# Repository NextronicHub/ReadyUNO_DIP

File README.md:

# ReadyUNO_DIP
## Description
READY-UNO is the best board to start your personal electronics projects, it is built upon the famous ARDUINO UNO, so it shares its simplicity and its flexibility. It contains also a BreadBoard with different interfaces of communication (SPI, UART, I2C and Serial communication) for easy development.
The READY-UNO can be programmed over a Serial Communication, using the ARDUINO IDE.
The READY-UNO can be powered through the barrel jack. The on-board power regulator can handle anything from 7 to 15VDC.
## Features
•	ATmega328 microcontroller with Optiboot (UNO) Bootloader                                                                         
•	Input voltage : 7 to 15V                                                                                                         
•	0-5V outputs                                                                                                                     
•	14 Digital I/O Pins (6 PWM outputs)                                                                                              
•	6 Analog Inputs                                                                                                                  
•	ISP Header                                                                                                                       
•	32k Flash Memory                                                                                                                 
•	16MHz Clock Speed                                                                                                                
•	All SMD Construction                                                                                                             
•	R3 Shield Compatible                                                                                                             
•	BreadBoard.                                                                                                                      
•	Red PCB.                                                                                                                         
•	I2C, UART and SPI.                                                                                                               
## Repository Contents

/Hardware - Design files (.brd, .sch)  
/Documentation - datasheet and examples

## Product Versions

ReadyUNO-DIP-V1 first release

## License Information

The hardware is released under [Creative Commons ShareAlike 4.0 International](https://creativecommons.org/licenses/by-sa/4.0/).

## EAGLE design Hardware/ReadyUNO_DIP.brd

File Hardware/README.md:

# Nextronic ReadyUNO DIP Design Files
The .sch and .brd files are Eagle CAD schematic and PCB design files from Nextronic. Eagle PCB Design | Schematic Editor, Layout Editor & Autorouter can be found at http://www.autodesk.com/products/eagle.

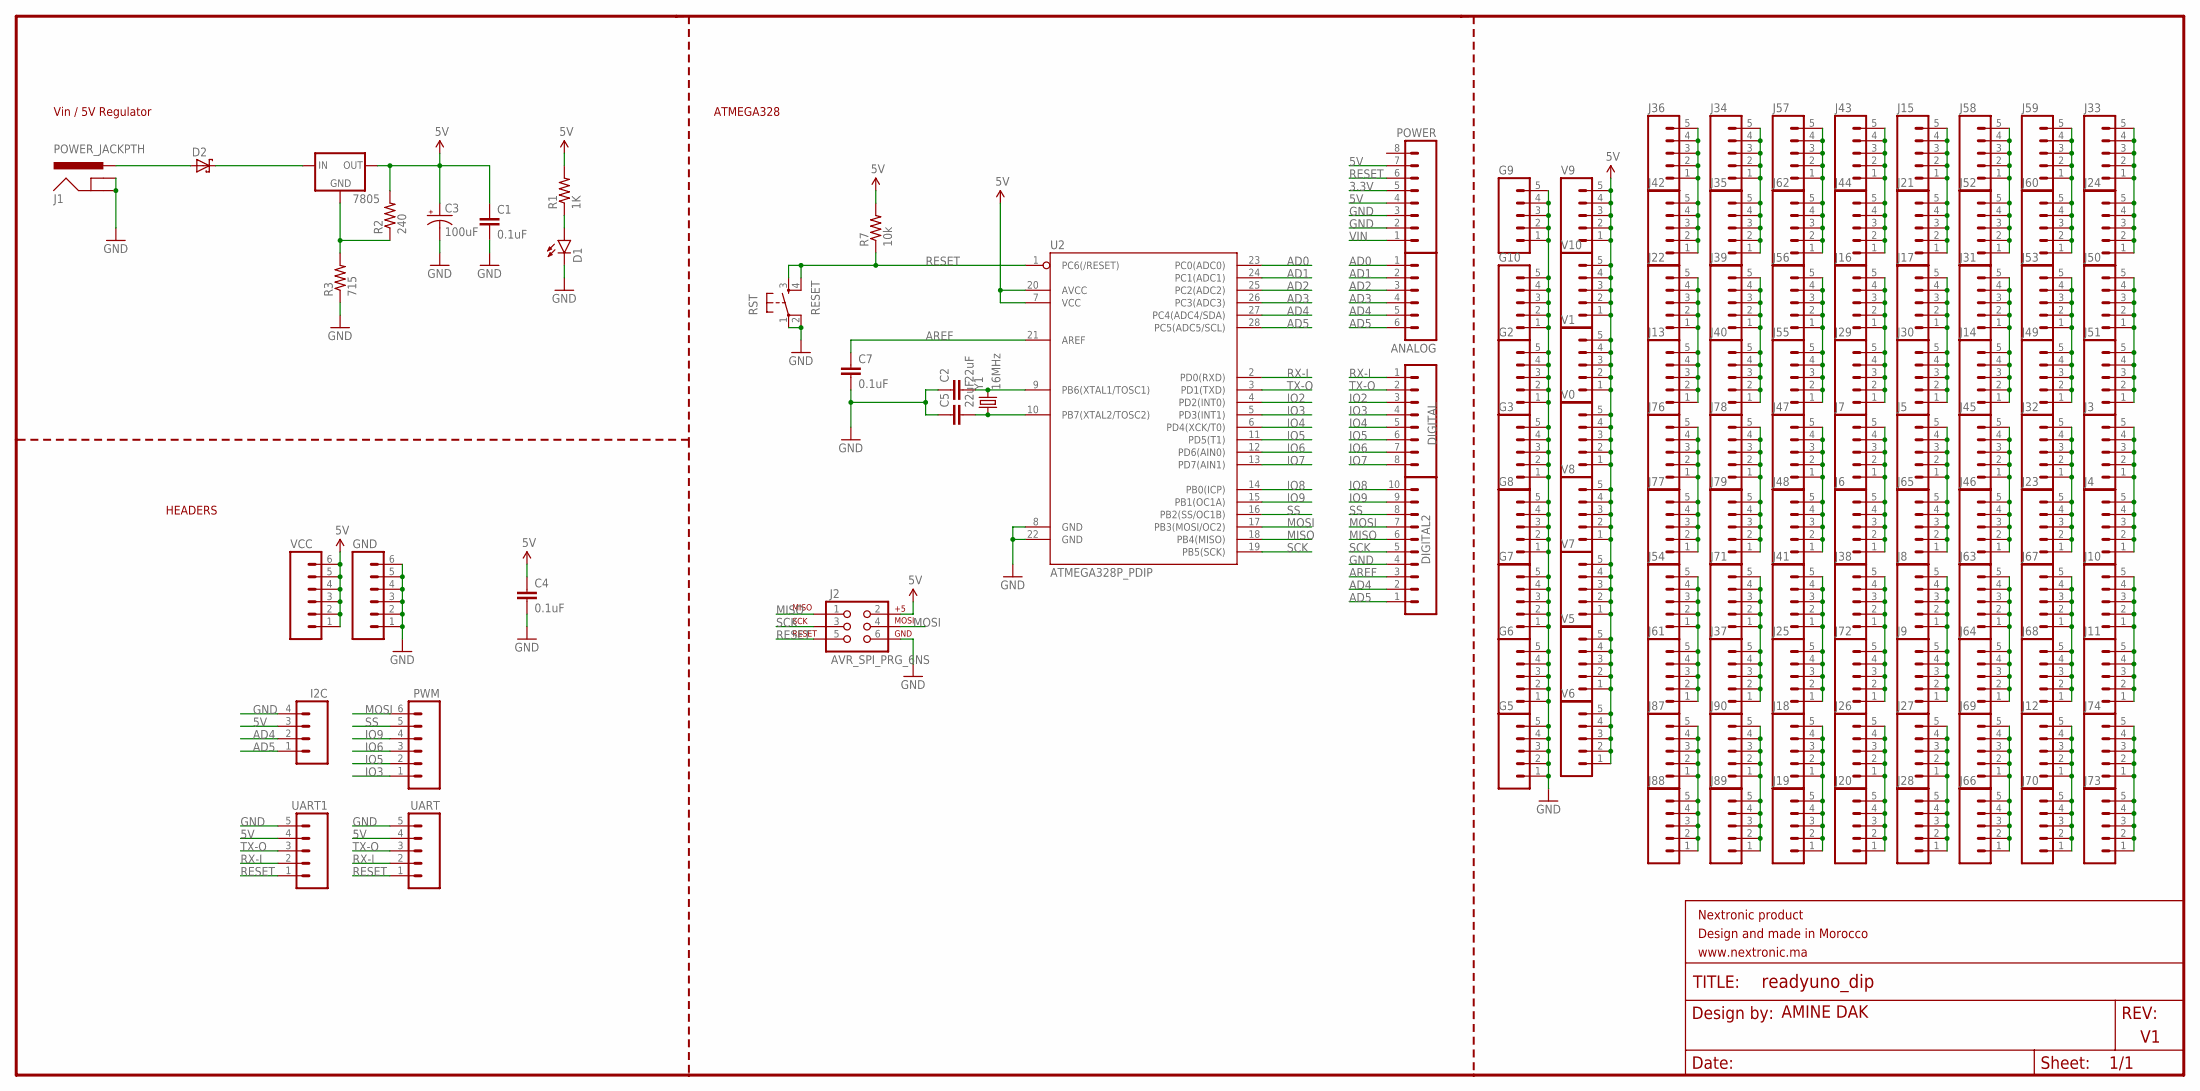
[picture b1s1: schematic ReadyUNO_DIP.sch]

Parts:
7805: V_REG_78XX-TO-220; TO-220-ALT
ANALOG: M06SILK_FEMALE_PTH; 1X06
C1, C4, C7: 0.1uF; CAP-PTH-SMALLEZ; MPN MCRR25104X7RK0050
C2, C5: 22uF; CAP-PTH-SMALLEZ; MPN MCGPR100V226M8X11
C3: 100uF; CPOL-RADIAL-100UF-25V; MPN MCGPR25V107M6.3X11
D1: LED-3MM-NO_SILK; LED3MM-NS
D2: SCHOTTKY-DIODEDO35-7; DIODE_DO35-7
DIGITAL: M08SILK_FEMALE_PTH; 1X08
DIGITAL2: M10SILK_FEMALE_PTH; 1X10
FRAME1: FRAME-LETTER; CREATIVE_COMMONS
G2, G3, G5, G6, G7, G8, G9, G10: M05PTH; 1X05
GND: M06SILK_FEMALE_PTH; 1X06
I2C: M04PTH; 1X04
J1: POWER_JACKPTH; POWER_JACK_PTH
J2: AVR_SPI_PRG_6NS; 2X3-NS
J3, J4, J5, J6, J7, J8, J9, J10, J11, J12, J13, J14, J15, J16, J17, J18, J19, J20, J21, J22, J23, J24, J25, J26, J27, J28, J29, J30, J31, J32, J33, J34, J35, J36, J37, J38, J39, J40, J41, J42, J43, J44, J45, J46, J47, J48, J49, J50, J51, J52, J53, J54, J55, J56, J57, J58, J59, J60, J61, J62, J63, J64, J65, J66, J67, J68, J69, J70, J71, J72, J73, J74, J76, J77, J78, J79, J87, J88, J89, J90: M05PTH; 1X05
POWER: M08SILK_FEMALE_PTH; 1X08
PWM: M06SILK_FEMALE_PTH; 1X06
R1: 1K; AXIAL-0.3; MPN MCRE000037
R2: 240; AXIAL-0.3; MPN MFR4-240RFI
R3: 715; AXIAL-0.3; MPN YR1B715RCC
R7: 10k; AXIAL-0.3
RST: RESET; TACTILE-PTH
U2: ATMEGA328P_PDIP; DIL28-3; MPN ATMEGA328-PU
UART, UART1: M05PTH; 1X05
V0, V1, V5, V6, V7, V8, V9, V10: M05PTH; 1X05
VCC: M06SILK_FEMALE_PTH; 1X06
Y1: 16MHz; HC49US; MPN AS-16.000-18

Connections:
3.3V: POWER.5
5V: 7805.OUT, C1.1, C3.1 (+), C4.1, I2C.3, J2.2, POWER.4, POWER.7, R1.P$2 (2), R2.P$2 (2), R7.P$2 (2), U2.7 (VCC), U2.20 (AVCC), UART.4, UART1.4, V0.1, V0.2, V0.3, V0.4, V0.5, V1.1, V1.2, V1.3, V1.4, V1.5, V5.1, V5.2, V5.3, V5.4, V5.5, V6.1, V6.2, V6.3, V6.4, V6.5, V7.1, V7.2, V7.3, V7.4, V7.5, V8.1, V8.2, V8.3, V8.4, V8.5, V9.1, V9.2, V9.3, V9.4, V9.5, V10.1, V10.2, V10.3, V10.4, V10.5, VCC.1, VCC.2, VCC.3, VCC.4, VCC.5, VCC.6
AD0: ANALOG.1, U2.23 (PC0(ADC0))
AD1: ANALOG.2, U2.24 (PC1(ADC1))
AD2: ANALOG.3, U2.25 (PC2(ADC2))
AD3: ANALOG.4, U2.26 (PC3(ADC3))
AD4: ANALOG.5, DIGITAL2.2, I2C.2, U2.27 (PC4(ADC4/SDA))
AD5: ANALOG.6, DIGITAL2.1, I2C.1, U2.28 (PC5(ADC5/SCL))
AREF: C7.1, DIGITAL2.3, U2.21 (AREF)
GND: C1.2, C2.1, C3.2 (-), C4.2, C5.1, C7.2, D1.K (C), DIGITAL2.4, G2.1, G2.2, G2.3, G2.4, G2.5, G3.1, G3.2, G3.3, G3.4, G3.5, G5.1, G5.2, G5.3, G5.4, G5.5, G6.1, G6.2, G6.3, G6.4, G6.5, G7.1, G7.2, G7.3, G7.4, G7.5, G8.1, G8.2, G8.3, G8.4, G8.5, G9.1, G9.2, G9.3, G9.4, G9.5, G10.1, G10.2, G10.3, G10.4, G10.5, GND.1, GND.2, GND.3, GND.4, GND.5, GND.6, I2C.4, J1.GND, J1.GNDBREAK, J2.6, POWER.2, POWER.3, R3.P$1 (1), RST.1, RST.2, U2.8 (GND), U2.22 (GND), UART.5, UART1.5
IO2: DIGITAL.3, U2.4 (PD2(INT0))
IO3: DIGITAL.4, PWM.1, U2.5 (PD3(INT1))
IO4: DIGITAL.5, U2.6 (PD4(XCK/T0))
IO5: DIGITAL.6, PWM.2, U2.11 (PD5(T1))
IO6: DIGITAL.7, PWM.3, U2.12 (PD6(AIN0))
IO7: DIGITAL.8, U2.13 (PD7(AIN1))
IO8: DIGITAL2.10, U2.14 (PB0(ICP))
IO9: DIGITAL2.9, PWM.4, U2.15 (PB1(OC1A))
MISO: DIGITAL2.6, J2.1, U2.18 (PB4(MISO))
MOSI: DIGITAL2.7, J2.4, PWM.6, U2.17 (PB3(MOSI/OC2))
unnamed: 7805.GND, R2.P$1 (1), R3.P$2 (2)
unnamed: J18.1, J18.2, J18.3, J18.4, J18.5, J19.1, J19.2, J19.3, J19.4, J19.5
unnamed: J87.1, J87.2, J87.3, J87.4, J87.5, J88.1, J88.2, J88.3, J88.4, J88.5
unnamed: D1.A, R1.P$1 (1)
unnamed: J89.1, J89.2, J89.3, J89.4, J89.5, J90.1, J90.2, J90.3, J90.4, J90.5
unnamed: J37.1, J37.2, J37.3, J37.4, J37.5, J71.1, J71.2, J71.3, J71.4, J71.5
unnamed: C2.2, U2.9 (PB6(XTAL1/TOSC1)), Y1.2
unnamed: C5.2, U2.10 (PB7(XTAL2/TOSC2)), Y1.1
unnamed: J3.1, J3.2, J3.3, J3.4, J3.5, J4.1, J4.2, J4.3, J4.4, J4.5
unnamed: J20.1, J20.2, J20.3, J20.4, J20.5, J26.1, J26.2, J26.3, J26.4, J26.5
unnamed: J10.1, J10.2, J10.3, J10.4, J10.5, J11.1, J11.2, J11.3, J11.4, J11.5
unnamed: J76.1, J76.2, J76.3, J76.4, J76.5, J77.1, J77.2, J77.3, J77.4, J77.5
unnamed: J27.1, J27.2, J27.3, J27.4, J27.5, J28.1, J28.2, J28.3, J28.4, J28.5
unnamed: J25.1, J25.2, J25.3, J25.4, J25.5, J41.1, J41.2, J41.3, J41.4, J41.5
unnamed: J78.1, J78.2, J78.3, J78.4, J78.5, J79.1, J79.2, J79.3, J79.4, J79.5
unnamed: J66.1, J66.2, J66.3, J66.4, J66.5, J69.1, J69.2, J69.3, J69.4, J69.5
unnamed: J45.1, J45.2, J45.3, J45.4, J45.5, J46.1, J46.2, J46.3, J46.4, J46.5
unnamed: D2.A (C), J1.PWR
unnamed: J47.1, J47.2, J47.3, J47.4, J47.5, J48.1, J48.2, J48.3, J48.4, J48.5
unnamed: J12.1, J12.2, J12.3, J12.4, J12.5, J70.1, J70.2, J70.3, J70.4, J70.5
unnamed: J73.1, J73.2, J73.3, J73.4, J73.5, J74.1, J74.2, J74.3, J74.4, J74.5
unnamed: J54.1, J54.2, J54.3, J54.4, J54.5, J61.1, J61.2, J61.3, J61.4, J61.5
unnamed: J38.1, J38.2, J38.3, J38.4, J38.5, J72.1, J72.2, J72.3, J72.4, J72.5
unnamed: J24.1, J24.2, J24.3, J24.4, J24.5, J33.1, J33.2, J33.3, J33.4, J33.5
unnamed: J23.1, J23.2, J23.3, J23.4, J23.5, J32.1, J32.2, J32.3, J32.4, J32.5
unnamed: J67.1, J67.2, J67.3, J67.4, J67.5, J68.1, J68.2, J68.3, J68.4, J68.5
unnamed: J49.1, J49.2, J49.3, J49.4, J49.5, J53.1, J53.2, J53.3, J53.4, J53.5
unnamed: J59.1, J59.2, J59.3, J59.4, J59.5, J60.1, J60.2, J60.3, J60.4, J60.5
unnamed: J14.1, J14.2, J14.3, J14.4, J14.5, J31.1, J31.2, J31.3, J31.4, J31.5
unnamed: J17.1, J17.2, J17.3, J17.4, J17.5, J30.1, J30.2, J30.3, J30.4, J30.5
unnamed: J52.1, J52.2, J52.3, J52.4, J52.5, J58.1, J58.2, J58.3, J58.4, J58.5
unnamed: J50.1, J50.2, J50.3, J50.4, J50.5, J51.1, J51.2, J51.3, J51.4, J51.5
unnamed: J16.1, J16.2, J16.3, J16.4, J16.5, J29.1, J29.2, J29.3, J29.4, J29.5
unnamed: J43.1, J43.2, J43.3, J43.4, J43.5, J44.1, J44.2, J44.3, J44.4, J44.5
unnamed: J15.1, J15.2, J15.3, J15.4, J15.5, J21.1, J21.2, J21.3, J21.4, J21.5
unnamed: J36.1, J36.2, J36.3, J36.4, J36.5, J42.1, J42.2, J42.3, J42.4, J42.5
unnamed: J13.1, J13.2, J13.3, J13.4, J13.5, J22.1, J22.2, J22.3, J22.4, J22.5
unnamed: J6.1, J6.2, J6.3, J6.4, J6.5, J7.1, J7.2, J7.3, J7.4, J7.5
unnamed: J8.1, J8.2, J8.3, J8.4, J8.5, J9.1, J9.2, J9.3, J9.4, J9.5
unnamed: J34.1, J34.2, J34.3, J34.4, J34.5, J35.1, J35.2, J35.3, J35.4, J35.5
unnamed: J39.1, J39.2, J39.3, J39.4, J39.5, J40.1, J40.2, J40.3, J40.4, J40.5
unnamed: J5.1, J5.2, J5.3, J5.4, J5.5, J65.1, J65.2, J65.3, J65.4, J65.5
unnamed: J63.1, J63.2, J63.3, J63.4, J63.5, J64.1, J64.2, J64.3, J64.4, J64.5
unnamed: J57.1, J57.2, J57.3, J57.4, J57.5, J62.1, J62.2, J62.3, J62.4, J62.5
unnamed: J55.1, J55.2, J55.3, J55.4, J55.5, J56.1, J56.2, J56.3, J56.4, J56.5
unnamed: 7805.IN, D2.C (A)
RESET: J2.5, POWER.6, R7.P$1 (1), RST.3, RST.4, U2.1 (PC6(/RESET)), UART.1, UART1.1
RX-I: DIGITAL.1, U2.2 (PD0(RXD)), UART.2, UART1.2
SCK: DIGITAL2.5, J2.3, U2.19 (PB5(SCK))
SS: DIGITAL2.8, PWM.5, U2.16 (PB2(SS/OC1B))
TX-O: DIGITAL.2, U2.3 (PD1(TXD)), UART.3, UART1.3
VIN: POWER.1

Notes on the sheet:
Vin / 5V Regulator
ATMEGA328
AMINE DAK
HEADERS

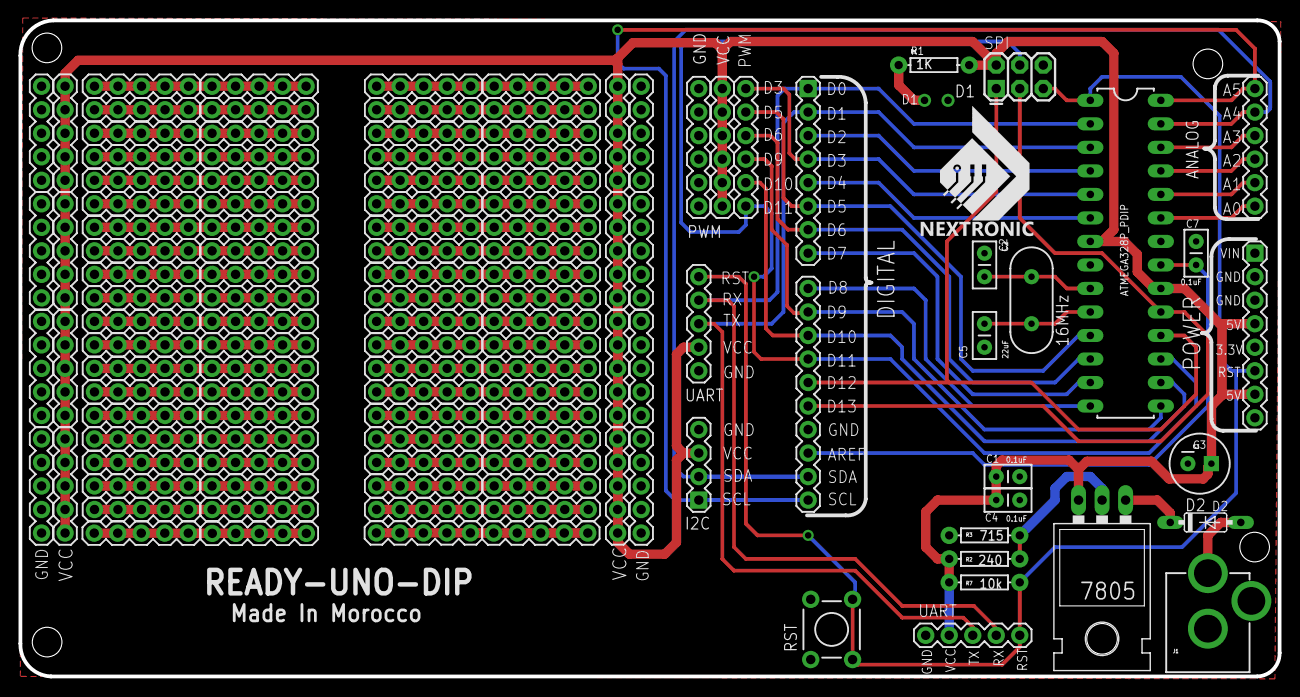
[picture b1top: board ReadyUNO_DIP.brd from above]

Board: 2 copper layers, 136.0 x 70.9 mm, 125 parts (0 on the bottom side), 70 nets.

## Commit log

2017-01-23 Rename ReadyUno_bootloader.hex to Firmware/ReadyUno_bootloader.hex
2017-01-23 Rename ReadyUNO_DIP.brd to Hardware/ReadyUNO_DIP.brd
2017-01-23 Rename ReadyUNO_DIP.sch to Hardware/ReadyUNO_DIP.sch
2017-01-23 Rename ReadyUNO_DIP.brd to ReadyUNO-DIP-v1.brd
2017-01-23 Rename ReadyUNO_DIP.sch to ReadyUNO-DIP-v1.sch
2017-01-23 Rename Nextronic-Arduino.brd to Hardware/ReadyUNO-DIP-v1.brd
2017-01-23 Rename Nextronic-Arduino.sch to Hardware/ReadyUNO-DIP-v1.sch

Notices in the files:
parts and their libraries:
SparkFun-Connectors: Licensing: Creative Commons ShareAlike 4.0 International - https://creativecommons.org/licenses/by-sa/4.0
SparkFun-Aesthetics: Released under the Creative Commons Attribution Share-Alike 4.0 License
